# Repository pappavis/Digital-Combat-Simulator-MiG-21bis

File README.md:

# Digital Combat Simulator: MiG-21bis designs
DCS: MiG-21bis KiCAD printed circuitboard designs.

Electronic diagrams for cockpit panels for http://DigitalCombatSimulator.com <br/>
by Michiel Erasmus <br/>

DCS: MIG-21bis panels by Michiel Erasmus<br/>
<br/>
<br/>
**Contact:** thebapodcast@gmail.com

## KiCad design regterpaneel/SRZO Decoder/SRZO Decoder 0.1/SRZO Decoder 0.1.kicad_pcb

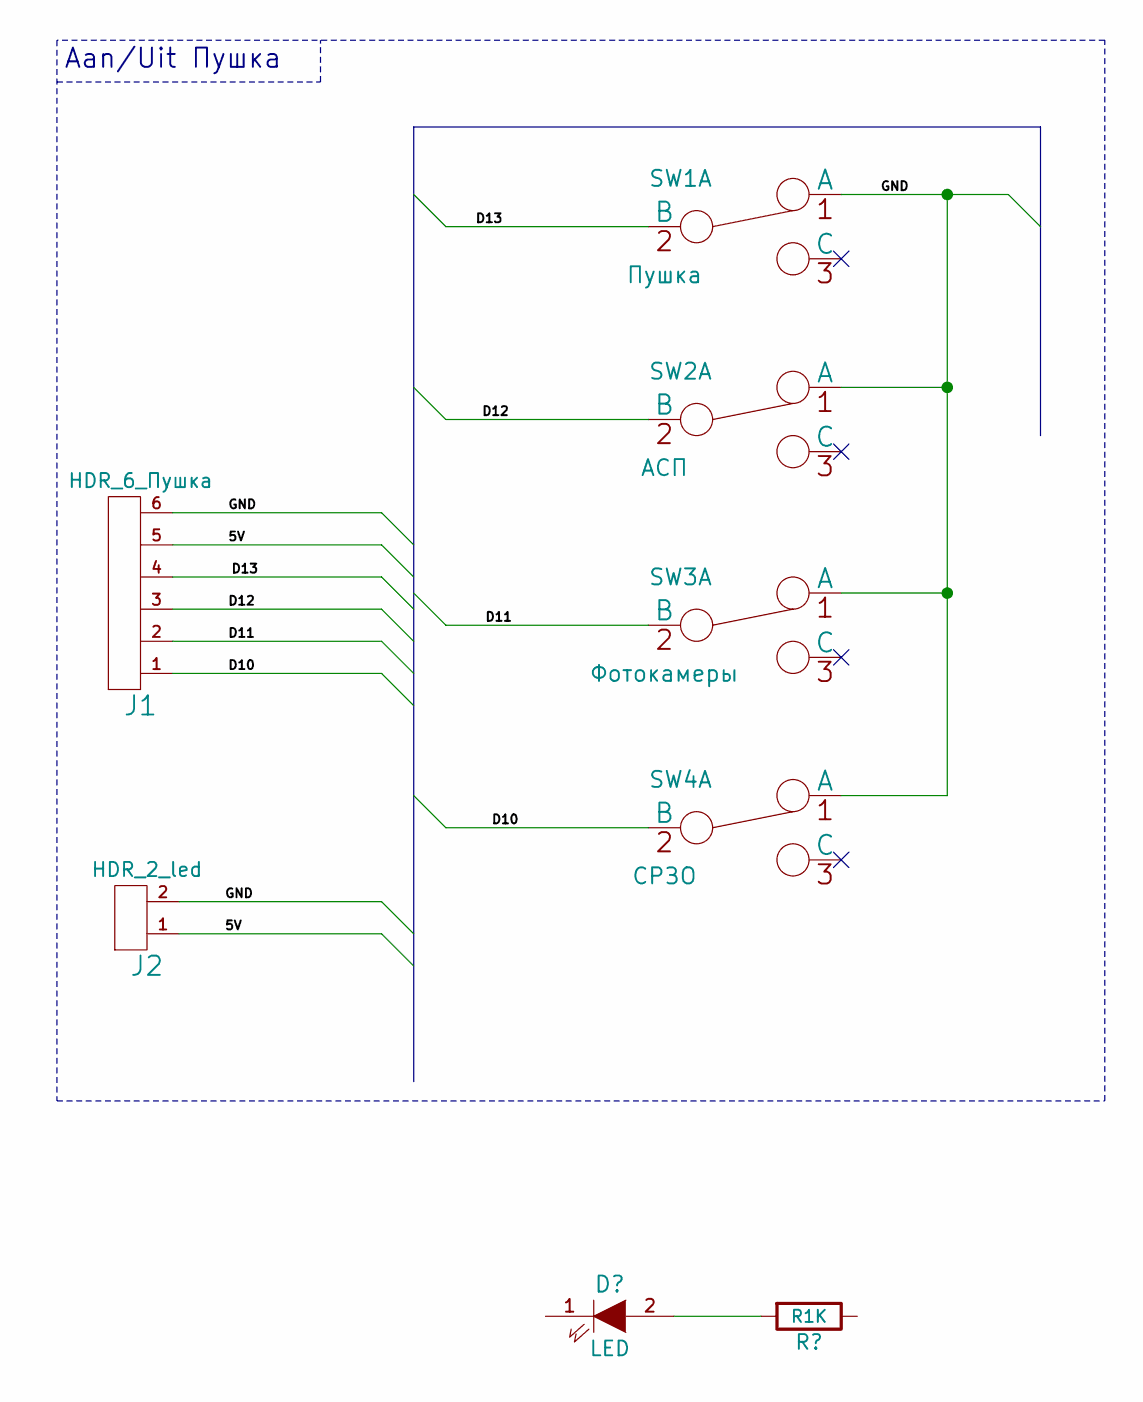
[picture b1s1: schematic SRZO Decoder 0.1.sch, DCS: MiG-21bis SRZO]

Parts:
J1: HDR_6_Пушка; Pin_Header_Straight_1x06
J2: HDR_2_led; Pin_Header_Straight_1x02_Pitch2.00mm
SW1: Пушка; switch_100sp5
SW2: АСП; switch_100sp5
SW3: Фотокамеры; switch_100sp5
SW4: СРЗО; switch_100sp5

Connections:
/5V: J1.5, J2.1
/D10: J1.1, SW4.2 (B)
/D11: J1.2, SW3.2 (B)
/D12: J1.3, SW2.2 (B)
/D13: J1.4, SW1.2 (B)
/GND: J1.6, J2.2, SW1.1 (A), SW2.1 (A), SW3.1 (A), SW4.1 (A)

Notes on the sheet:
Aan/Uit Пушка

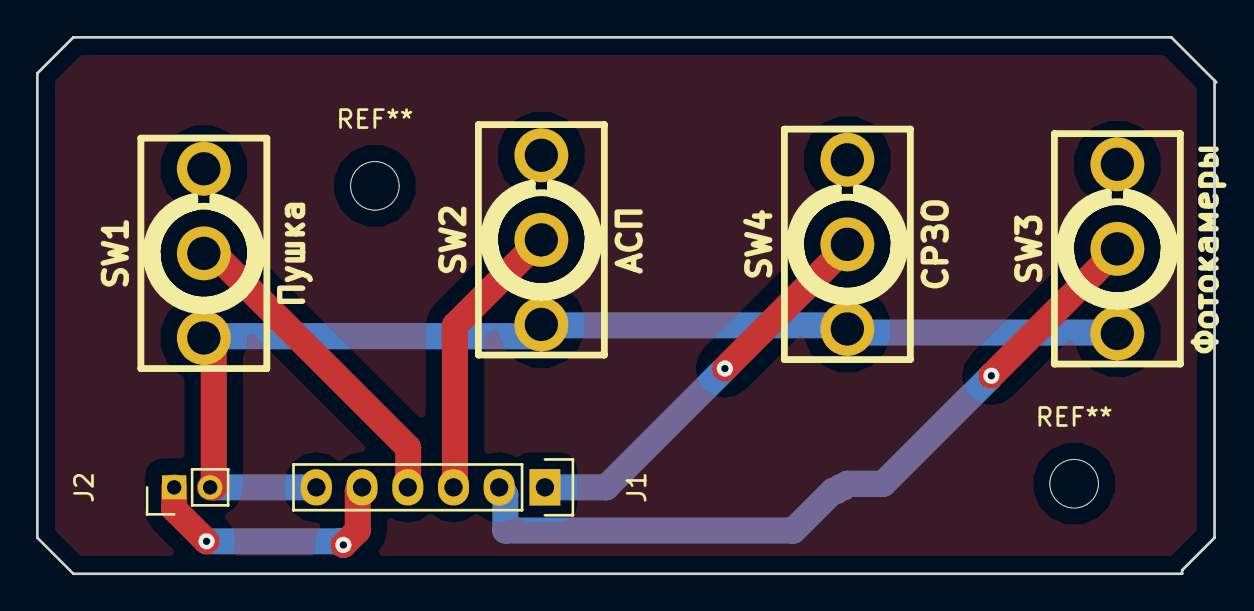
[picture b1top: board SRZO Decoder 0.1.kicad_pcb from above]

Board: 2 copper layers, 65.5 x 29.8 mm, 6 parts (0 on the bottom side), 6 nets.

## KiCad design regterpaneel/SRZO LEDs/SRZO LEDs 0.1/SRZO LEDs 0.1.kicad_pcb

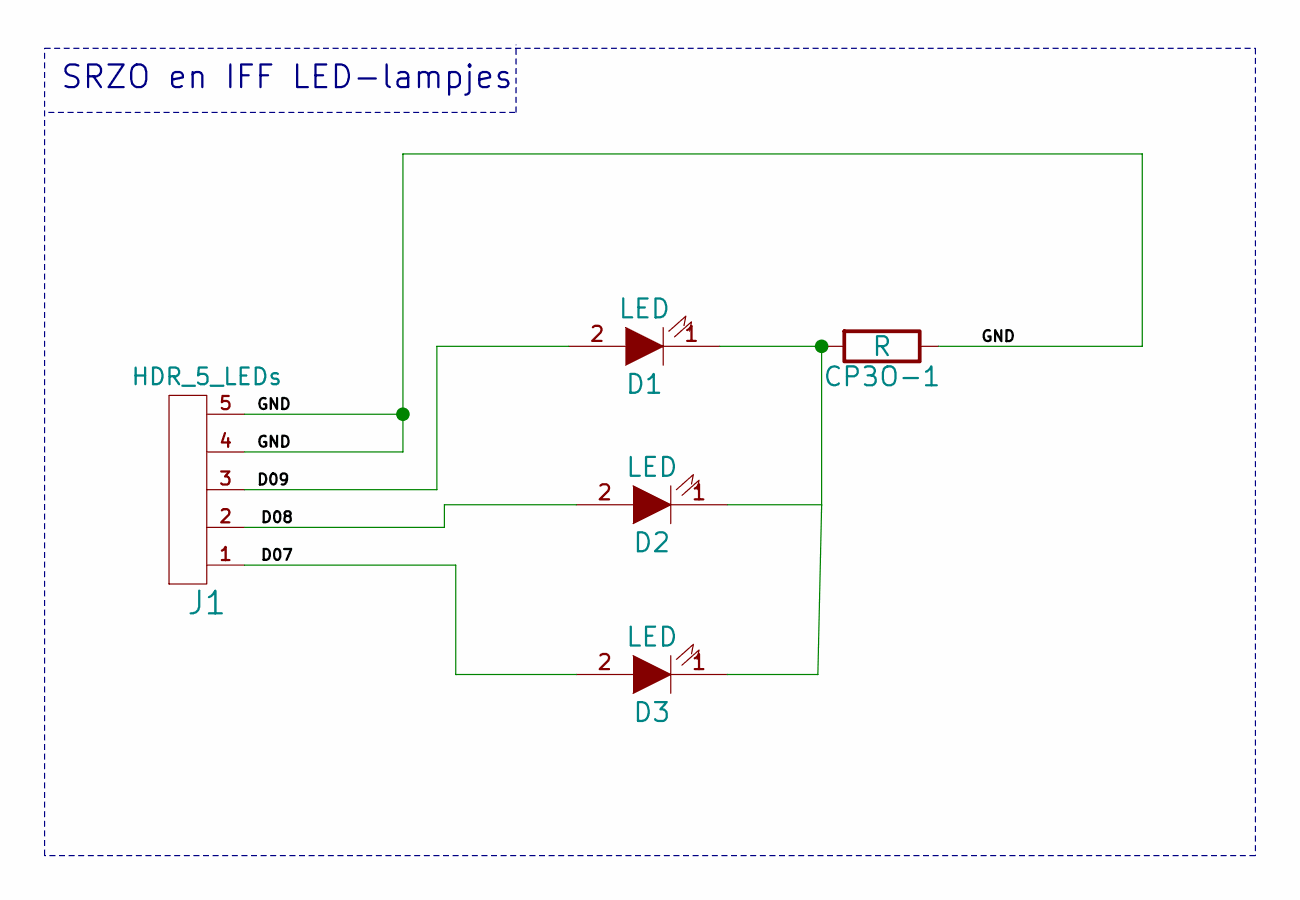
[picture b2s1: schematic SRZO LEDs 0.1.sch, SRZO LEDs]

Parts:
D1, D2, D3: LED; LED-5MM
J1: HDR_5_LEDs; Pin_Header_Straight_1x05
СРЗО-1: R; Resistor_Horizontal_RM7mm

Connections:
/D07: D3.2 (A), J1.1
/D08: D2.2 (A), J1.2
/D09: D1.2 (A), J1.3
/GND: J1.4, J1.5, СРЗО-1.1
unnamed: D1.1 (K), D2.1 (K), D3.1 (K), СРЗО-1.2

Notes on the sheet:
SRZO en IFF LED-lampjes

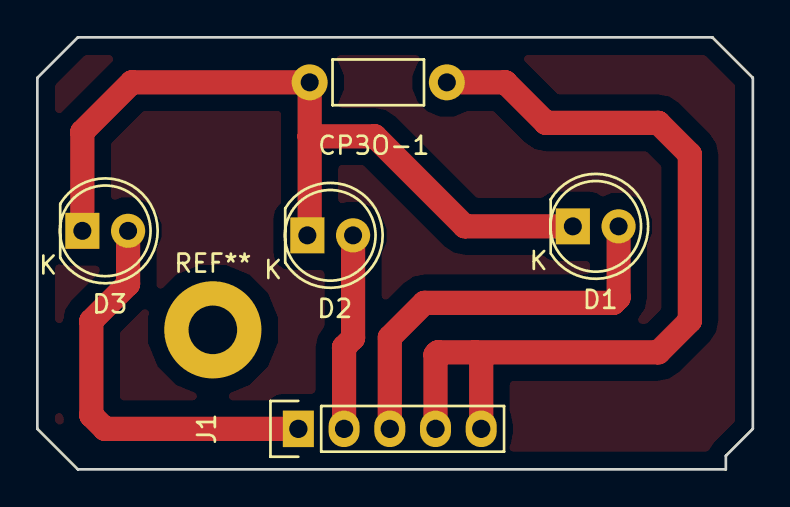
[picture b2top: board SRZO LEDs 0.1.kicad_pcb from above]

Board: 2 copper layers, 39.8 x 24.0 mm, 5 parts (0 on the bottom side), 5 nets.

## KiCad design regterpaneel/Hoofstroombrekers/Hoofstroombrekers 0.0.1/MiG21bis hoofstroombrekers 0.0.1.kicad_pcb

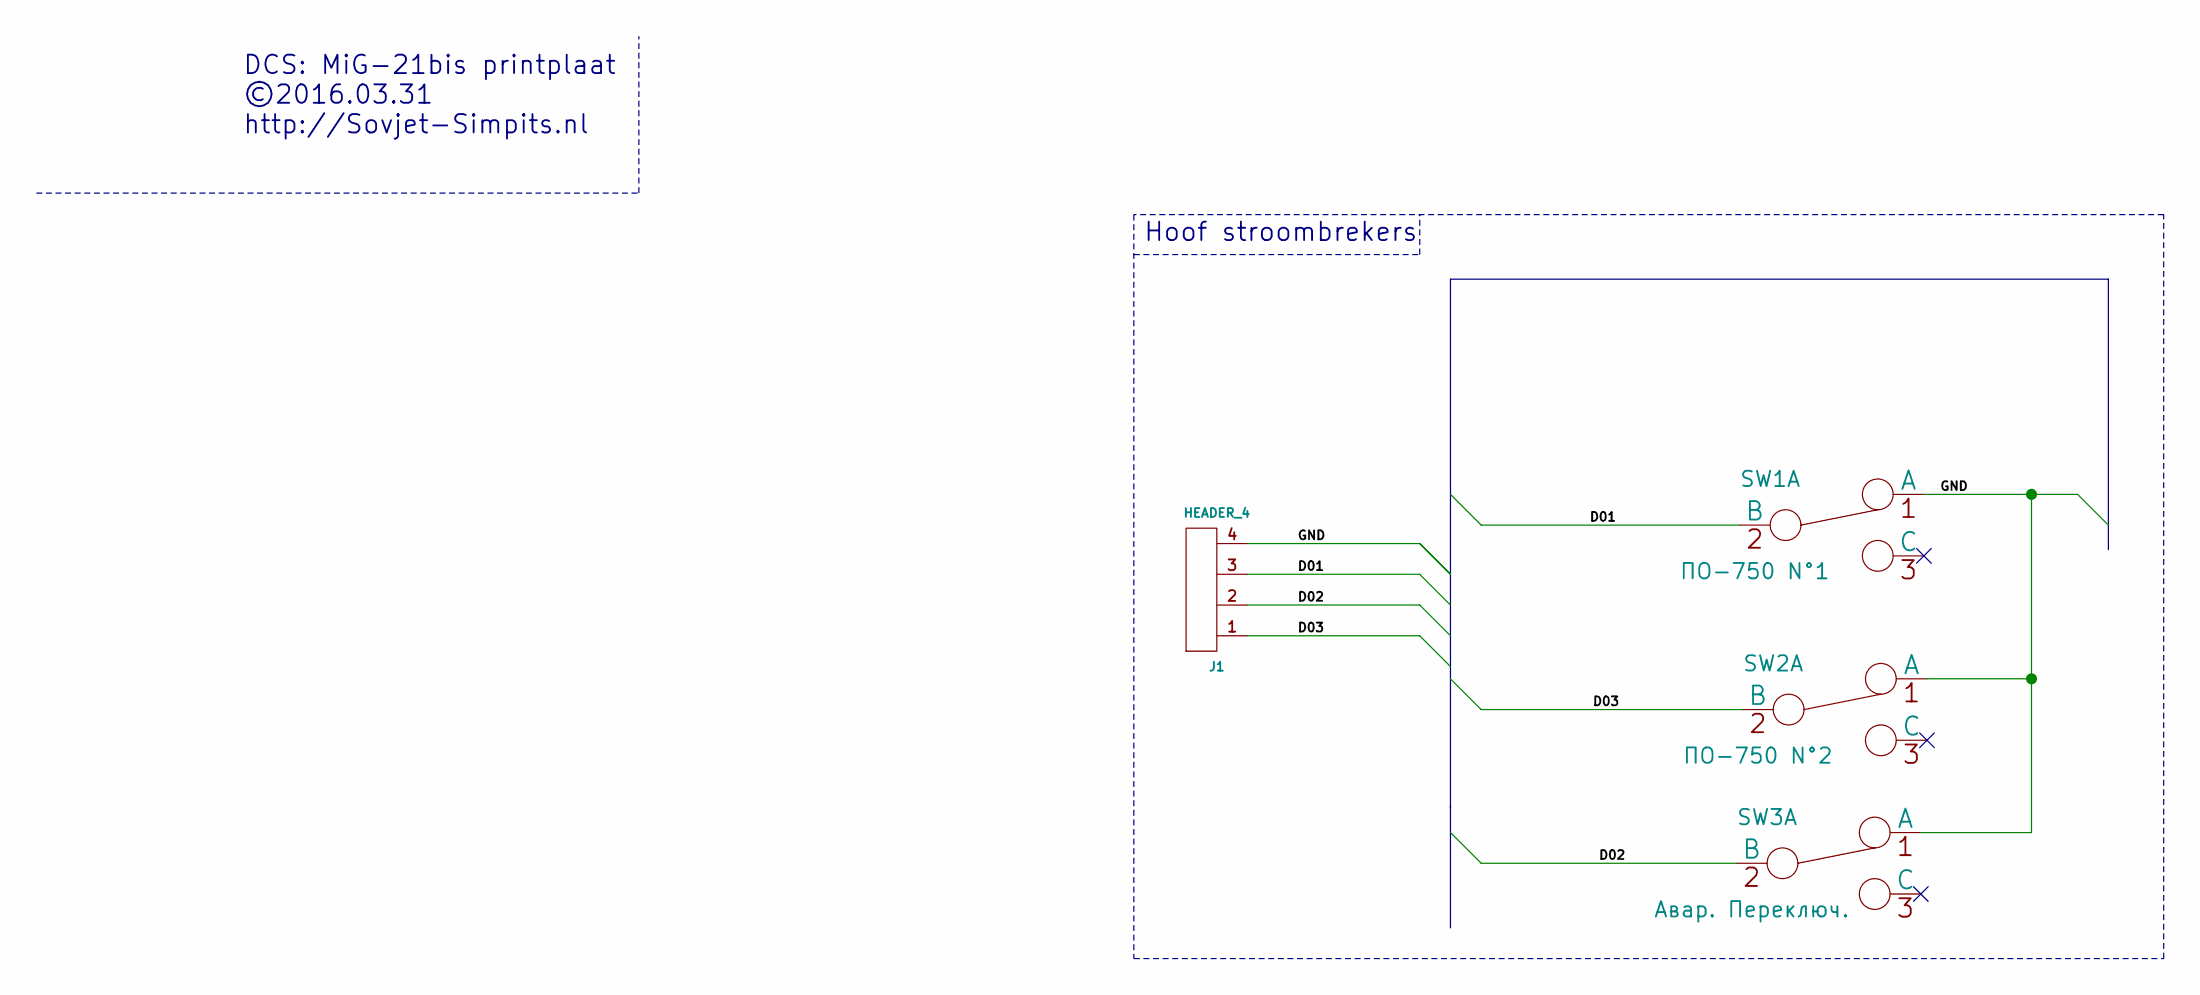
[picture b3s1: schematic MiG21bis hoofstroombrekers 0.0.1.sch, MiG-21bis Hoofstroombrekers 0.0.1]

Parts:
J1: HEADER_4; Pin_Header_Straight_1x04
SW1: ПО-750 N°1; switch_100sp5
SW2: ПО-750 N°2; switch_100sp5
SW3: Авар. Переключ.; switch_100sp5

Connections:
/D01: J1.3, SW1.2 (B)
/D02: J1.2, SW3.2 (B)
/D03: J1.1, SW2.2 (B)
/GND: J1.4, SW1.1 (A), SW2.1 (A), SW3.1 (A)

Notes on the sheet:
Hoof stroombrekers
DCS: MiG-21bis printplaat ©2016.03.31 http://Sovjet-Simpits.nl

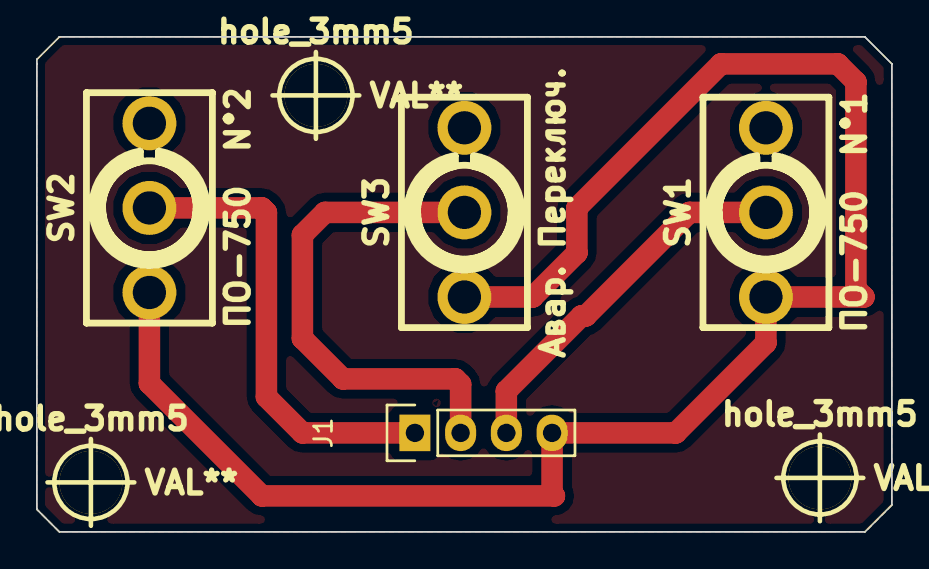
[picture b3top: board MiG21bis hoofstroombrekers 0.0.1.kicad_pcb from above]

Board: 2 copper layers, 47.5 x 27.5 mm, 7 parts (0 on the bottom side), 4 nets.

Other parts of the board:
hole_3mm5, hole_3mm5#2, hole_3mm5#3: VAL**; hole_3mm5

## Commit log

2016-07-03 :tada: Added .gitattributes
2016-07-03 DCS: MiG-21bisKiCAD project
    Schemas en GERBERs voor mijn DCS panels

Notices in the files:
regterpaneel/SRZO Decoder/SRZO Decoder 0.1/SRZO Decoder 0.1.kicad_pcb:
©Sovjet-Simpits.nl)
